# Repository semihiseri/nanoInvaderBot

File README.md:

# nanoInvaderBot
Invaderbot goes even smaller!

Current development is happening on FreeCAD 0.21 and KiCAD 7.0

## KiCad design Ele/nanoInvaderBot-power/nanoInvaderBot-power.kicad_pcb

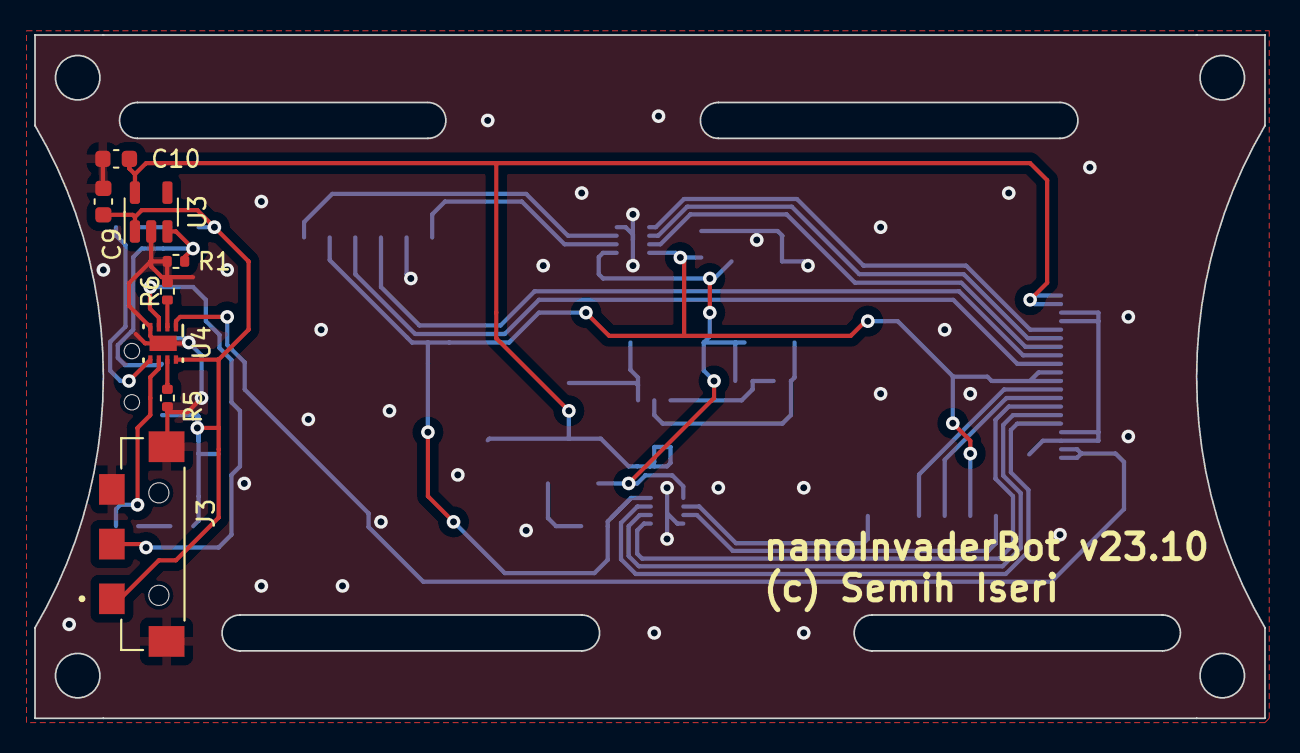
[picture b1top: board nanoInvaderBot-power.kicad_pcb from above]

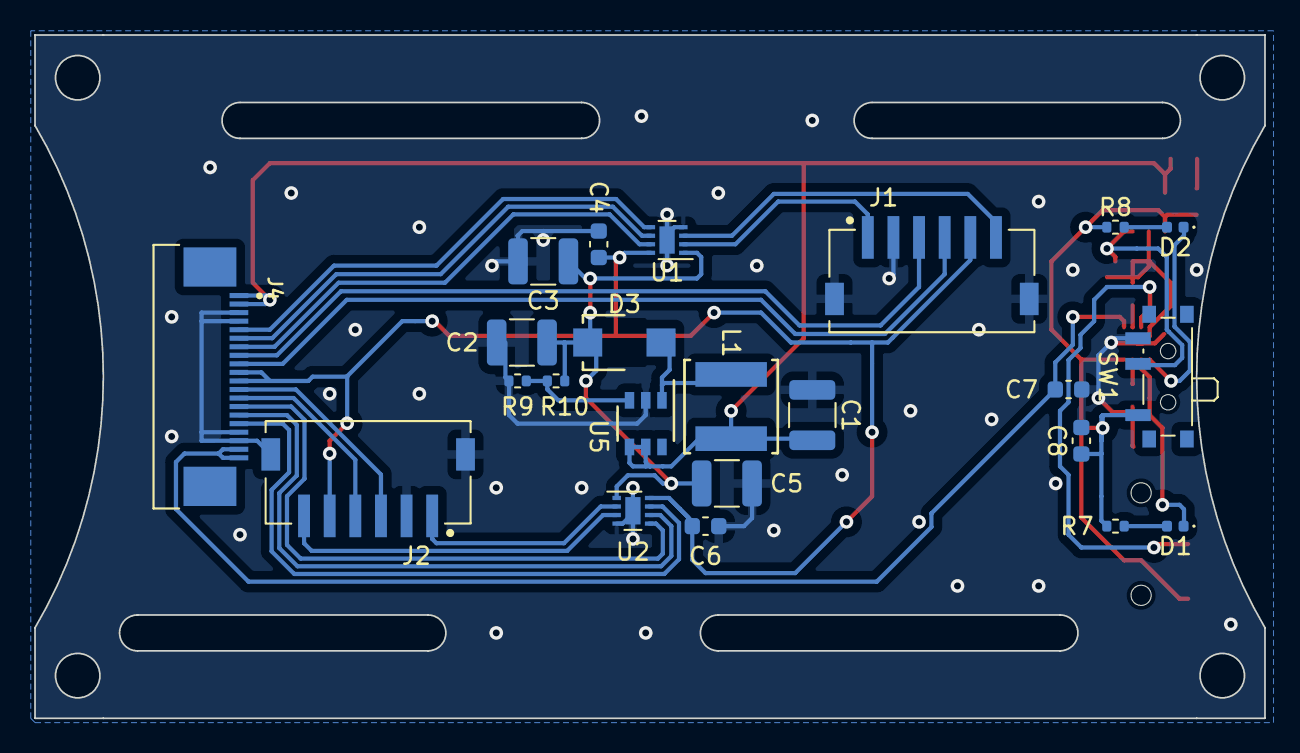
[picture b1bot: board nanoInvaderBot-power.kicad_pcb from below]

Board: 2 copper layers, 72.0 x 40.0 mm, 31 parts (23 on the bottom side), 30 nets.

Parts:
C1, C2, C3, C5: C; C_1210_3225Metric
C4, C6, C7, C8, C9, C10: C; C_0603_1608Metric
D1, D2: LED; LED_0402_1005Metric
D3: D; SDO_B120AF_DIO
J1, J2: S6B-ZR-SM4A-TF(LF)(SN); JST_S6B-ZR-SM4A-TF(LF)(SN)
J3: 1746142-1; TE_1746142-1
J4: Conn_01x20; TE_2-1734839-0
L1: L; IND_SWPA5040S_SNL
R1, R5, R6, R7, R8, R9, R10: R; R_0402_1005Metric
SW1: SW_SPDT; SW_SPDT_PCM12
U1, U2: WSON-8-1EP_2x2mm_P0.5mm_EP0.9x1.6mm
U3: SOT-23-5
U4: BQ25170DSGR; BQ25170DSGR_NV
U5: TLV61048DBVT; SOT23-6_DBV_TEX

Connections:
/3V3: C4.1, C6.1, J1.5, J2.5, J4.10, J4.11, U1.8 (VCC), U2.8 (VCC)
/12V: C2.1, C3.1, C5.1, D3.1 (K), R10.1, U1.1 (VM), U2.1 (VM)
/GND: C1.2, C2.2, C3.2, C4.2, C5.2, C6.2, C7.2, C8.2, C9.2, C10.2, J1.2, J1.SH1 (SHIELD), J1.SH2 (SHIELD), J2.2, J2.SH1 (SHIELD), J2.SH2 (SHIELD), J3.3, J3.SH1 (SHIELD1), J3.SH2 (SHIELD2), J4.3, J4.4, J4.17, J4.18, R1.2, R5.2, R6.2, R9.2, SW1.3 (C), U1.4 (GND), U1.9 (Thermal), U2.4 (GND), U2.9 (Thermal), U3.2 (Vss), U4.4 (GND), U4.9 (PAD), U5.2 (GND)
/MOTOR1_A: J1.1, U1.2 (OUT1)
/MOTOR1_A_MCU: J4.6, U1.6 (IN1)
/MOTOR1_B: J1.6, U1.3 (OUT2)
/MOTOR1_B_MCU: J4.5, U1.5 (IN2)
/MOTOR1_ENC1: J1.3, J4.8
/MOTOR1_ENC2: J1.4, J4.9
/MOTOR1_EN_MCU: J4.7, U1.7 (nSLEEP)
/MOTOR2_A: J2.1, U2.2 (OUT1)
/MOTOR2_A_MCU: J4.15, U2.6 (IN1)
/MOTOR2_B: J2.6, U2.3 (OUT2)
/MOTOR2_B_MCU: J4.14, U2.5 (IN2)
/MOTOR2_ENC1: J2.3, J4.12
/MOTOR2_ENC2: J2.4, J4.13
/MOTOR2_EN_MCU: J4.16, U2.7 (nSLEEP)
/SYS_EN: R1.1, SW1.2 (B), U3.3 (CE)
/TBATT: J3.2, U4.3 (TS)
/VBATT: C8.1, C9.1, J3.1, R7.1, R8.1, SW1.1 (A), U3.1 (Vin), U4.8 (OUT)
/VSYS: C1.1, C10.1, J4.1, J4.2, L1.2, U3.5 (Vout), U5.4 (EN), U5.5 (VIN)
/VUSB: C7.1, J4.19, J4.20, U4.1 (IN)
unnamed: D1.2 (A), R7.2
unnamed: D1.1 (K), U4.6 (PG_N)
unnamed: D2.2 (A), R8.2
unnamed: D2.1 (K), U4.5 (STAT)
unnamed: D3.2 (A), L1.1, U5.1 (SW)
unnamed: R6.1, U4.2 (ISET)
unnamed: R5.1, U4.7 (VSET)
unnamed: R9.1, R10.2, U5.3 (FB)

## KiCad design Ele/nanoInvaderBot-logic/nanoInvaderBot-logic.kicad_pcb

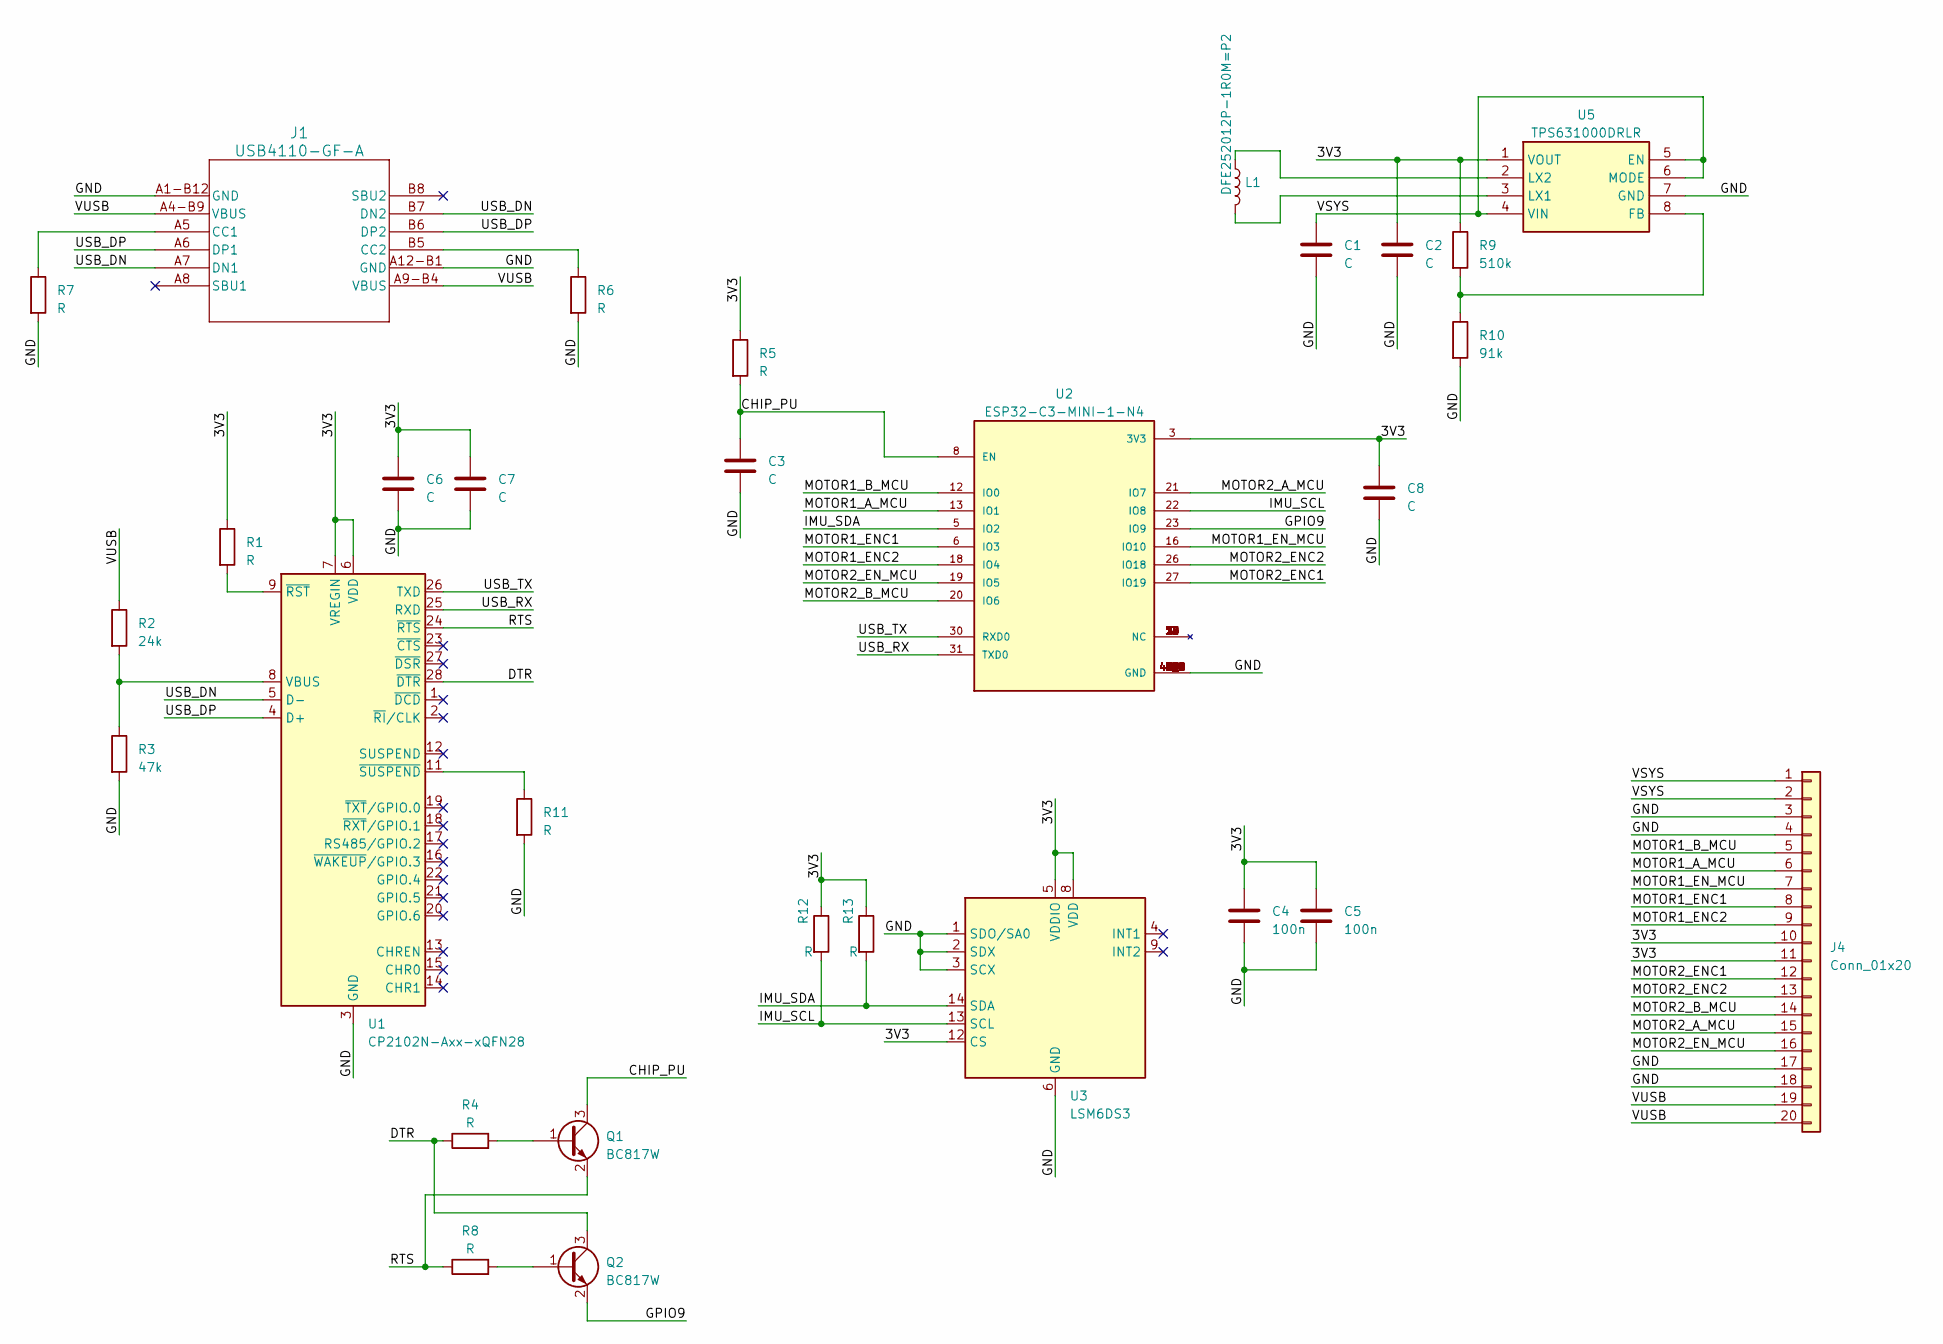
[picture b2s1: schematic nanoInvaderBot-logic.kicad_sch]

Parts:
C1, C2, C6, C7, C8: C; C_0805_2012Metric
C3: C; C_0603_1608Metric
C4, C5: 100n; C_0603_1608Metric
J1: USB4110-GF-A; USB4110-GF-A_GCT
J4: Conn_01x20; TE_2-1734839-0
L1: DFE252012P-1R0M=P2; L_2512_6332Metric
Q1, Q2: BC817W; SOT-323_SC-70
R1, R4, R5, R6, R7, R8, R11, R12, R13: R; R_0402_1005Metric
R2: 24k; R_0402_1005Metric
R3: 47k; R_0402_1005Metric
R9: 510k; R_0402_1005Metric
R10: 91k; R_0402_1005Metric
U1: CP2102N-Axx-xQFN28; QFN-28-1EP_5x5mm_P0.5mm_EP3.35x3.35mm
U2: ESP32-C3-MINI-1-N4; XCVR_ESP32-C3-MINI-1-N4; PARTREV v1.0
U3: LSM6DS3; LGA-14_3x2.5mm_P0.5mm_LayoutBorder3x4y
U5: TPS631000DRLR; SOTFL50P160X60-8N; Mouser Part Number 595-TPS631000DRLR

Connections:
/3V3: C2.1, C4.1, C5.1, C6.2, C7.2, C8.2, J4.10, J4.11, R1.1, R5.1, R9.1, R12.1, R13.1, U1.6 (VDD), U1.7 (VREGIN), U2.3 (3V3), U3.5 (VDDIO), U3.8 (VDD), U3.12 (CS), U5.1 (VOUT)
/CHIP_PU: C3.1, Q1.3 (C), R5.2, U2.8 (EN)
/DTR: Q2.3 (C), R4.1, U1.28 (~DTR)
/GND: C1.2, C2.2, C3.2, C4.2, C5.2, C6.1, C7.1, C8.1, J1.A1-B12 (GND), J1.A12-B1 (GND), J4.3, J4.4, J4.17, J4.18, R3.2, R6.2, R7.2, R10.2, R11.2, U1.3 (GND), U1.29 (GND), U2.1 (GND), U2.2 (GND), U2.11 (GND), U2.14 (GND), U2.36 (GND), U2.37 (GND), U2.38 (GND), U2.39 (GND), U2.40 (GND), U2.41 (GND), U2.42 (GND), U2.43 (GND), U2.44 (GND), U2.45 (GND), U2.46 (GND), U2.47 (GND), U2.48 (GND), U2.49_1 (GND), U2.49_2 (GND), U2.49_3 (GND), U2.49_4 (GND), U2.49_5 (GND), U2.49_6 (GND), U2.49_7 (GND), U2.49_8 (GND), U2.49_9 (GND), U2.50 (GND), U2.51 (GND), U2.52 (GND), U2.53 (GND), U3.1 (SDO/SA0), U3.2 (SDX), U3.3 (SCX), U3.6 (GND), U3.7 (GND), U5.7 (GND)
/GPIO9: Q2.2 (E), U2.23 (IO9)
/IMU_SCL: R12.2, U2.22 (IO8), U3.13 (SCL)
/IMU_SDA: R13.2, U2.5 (IO2), U3.14 (SDA)
/MOTOR1_A_MCU: J4.6, U2.13 (IO1)
/MOTOR1_B_MCU: J4.5, U2.12 (IO0)
/MOTOR1_ENC1: J4.8, U2.6 (IO3)
/MOTOR1_ENC2: J4.9, U2.18 (IO4)
/MOTOR1_EN_MCU: J4.7, U2.16 (IO10)
/MOTOR2_A_MCU: J4.15, U2.21 (IO7)
/MOTOR2_B_MCU: J4.14, U2.20 (IO6)
/MOTOR2_ENC1: J4.12, U2.27 (IO19)
/MOTOR2_ENC2: J4.13, U2.26 (IO18)
/MOTOR2_EN_MCU: J4.16, U2.19 (IO5)
/RTS: Q1.2 (E), R8.1, U1.24 (~RTS)
/USB_DN: J1.A7 (DN1), J1.B7 (DN2), U1.5 (D-)
/USB_DP: J1.A6 (DP1), J1.B6 (DP2), U1.4 (D+)
/USB_RX: U1.25 (RXD), U2.31 (TXD0)
/USB_TX: U1.26 (TXD), U2.30 (RXD0)
/VSYS: C1.1, J4.1, J4.2, U5.4 (VIN), U5.5 (EN), U5.6 (MODE)
/VUSB: J1.A4-B9 (VBUS), J1.A9-B4 (VBUS), J4.19, J4.20, R2.1
unnamed: J1.A5 (CC1), R7.1
unnamed: J1.B5 (CC2), R6.1
unnamed: Q1.1 (B), R4.2
unnamed: Q2.1 (B), R8.2
unnamed: R2.2, R3.1, U1.8 (VBUS)
unnamed: R1.2, U1.9 (~RST)
unnamed: R11.1, U1.11 (~SUSPEND)
unnamed: R9.2, R10.1, U5.8 (FB)
unnamed: L1.2, U5.3 (LX1)
unnamed: L1.1, U5.2 (LX2)

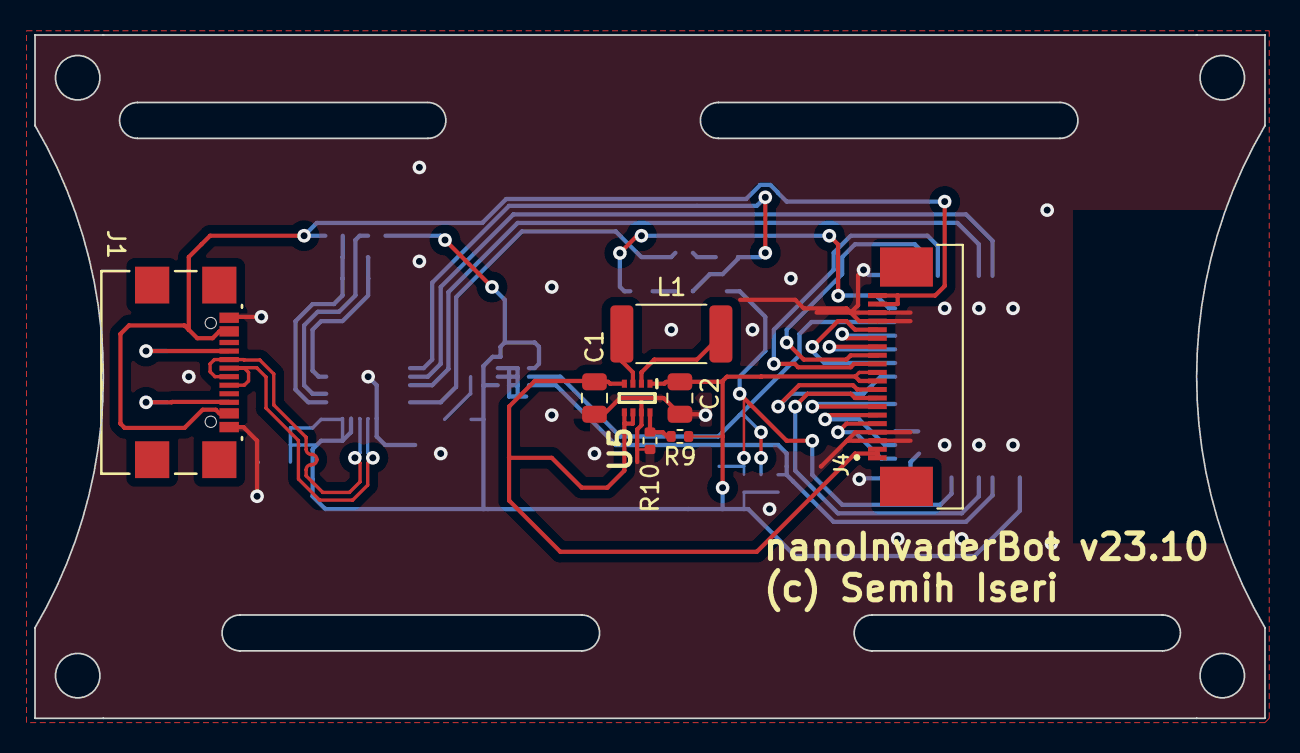
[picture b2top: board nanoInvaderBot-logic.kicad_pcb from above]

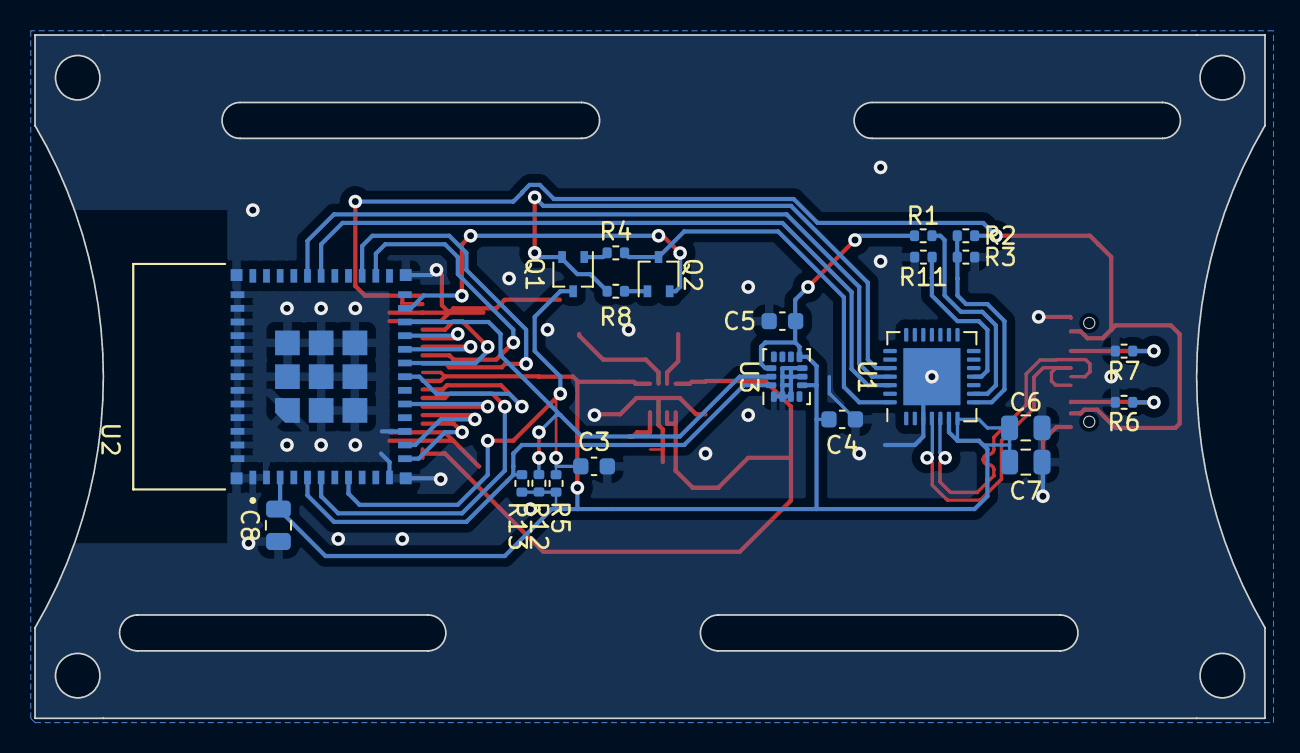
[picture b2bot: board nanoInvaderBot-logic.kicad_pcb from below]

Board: 2 copper layers, 72.0 x 40.0 mm, 30 parts (22 on the bottom side), 34 nets.

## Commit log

2023-08-23 Concept design with simple models
2023-09-09 Added bare holders for GW1812
2023-09-24 Power board main components added
2023-10-13 Placed components in power board
2023-10-17 Intermediate state -power layer almost done
2023-10-19 Power side done, logic side cleanup
2023-11-01 Intermediate state after v23.10
2023-11-03 Modifications for first running proto
